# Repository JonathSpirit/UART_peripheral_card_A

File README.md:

# UART_peripheral_card_A

Copyright (C) 2021 Guillaume Guillet\
Licensed under CERN-OHL-W v2 or later

<table border="0px">
<tr>
<td>
This source describes Open Hardware and is licensed under the CERN-OHL-W v2 or later.
</td>
</tr>
<tr>
<td>
You may redistribute and modify this documentation and make products
using it under the terms of the CERN-OHL-W v2 (https:/cern.ch/cern-ohl).
This documentation is distributed WITHOUT ANY EXPRESS OR IMPLIED
WARRANTY, INCLUDING OF MERCHANTABILITY, SATISFACTORY QUALITY
AND FITNESS FOR A PARTICULAR PURPOSE. Please see the CERN-OHL-W v2
for applicable conditions.
</td>
</tr>
</table>

Made with [Kicad](https://kicad.org/)

## Description
A UART peripheral card compatible with [PP1 standard](https://github.com/JonathSpirit/GComputer_standard).
This is a homemade without any microcontroller UART board that can transmit and receive in fixed 9600 baud rate and full-duplex.

## Stats

\
\
\

## Main features

- Follow the [PP1](https://github.com/JonathSpirit/GComputer_standard) standard.

- Fixed 9600 baud rate.

- Full duplex.

- 1 byte receive/transmit buffer.

- Compatible CMOS/TTL logic level.

## Documents
[Schematics (.pdf)](documents/UART_peripheral_card_A_schematics.pdf)

[Materials (.pdf)](documents/UART_peripheral_card_A_materials.pdf)

## Contributing / Questions
Please see [Contributing file](CONTRIBUTING.md)

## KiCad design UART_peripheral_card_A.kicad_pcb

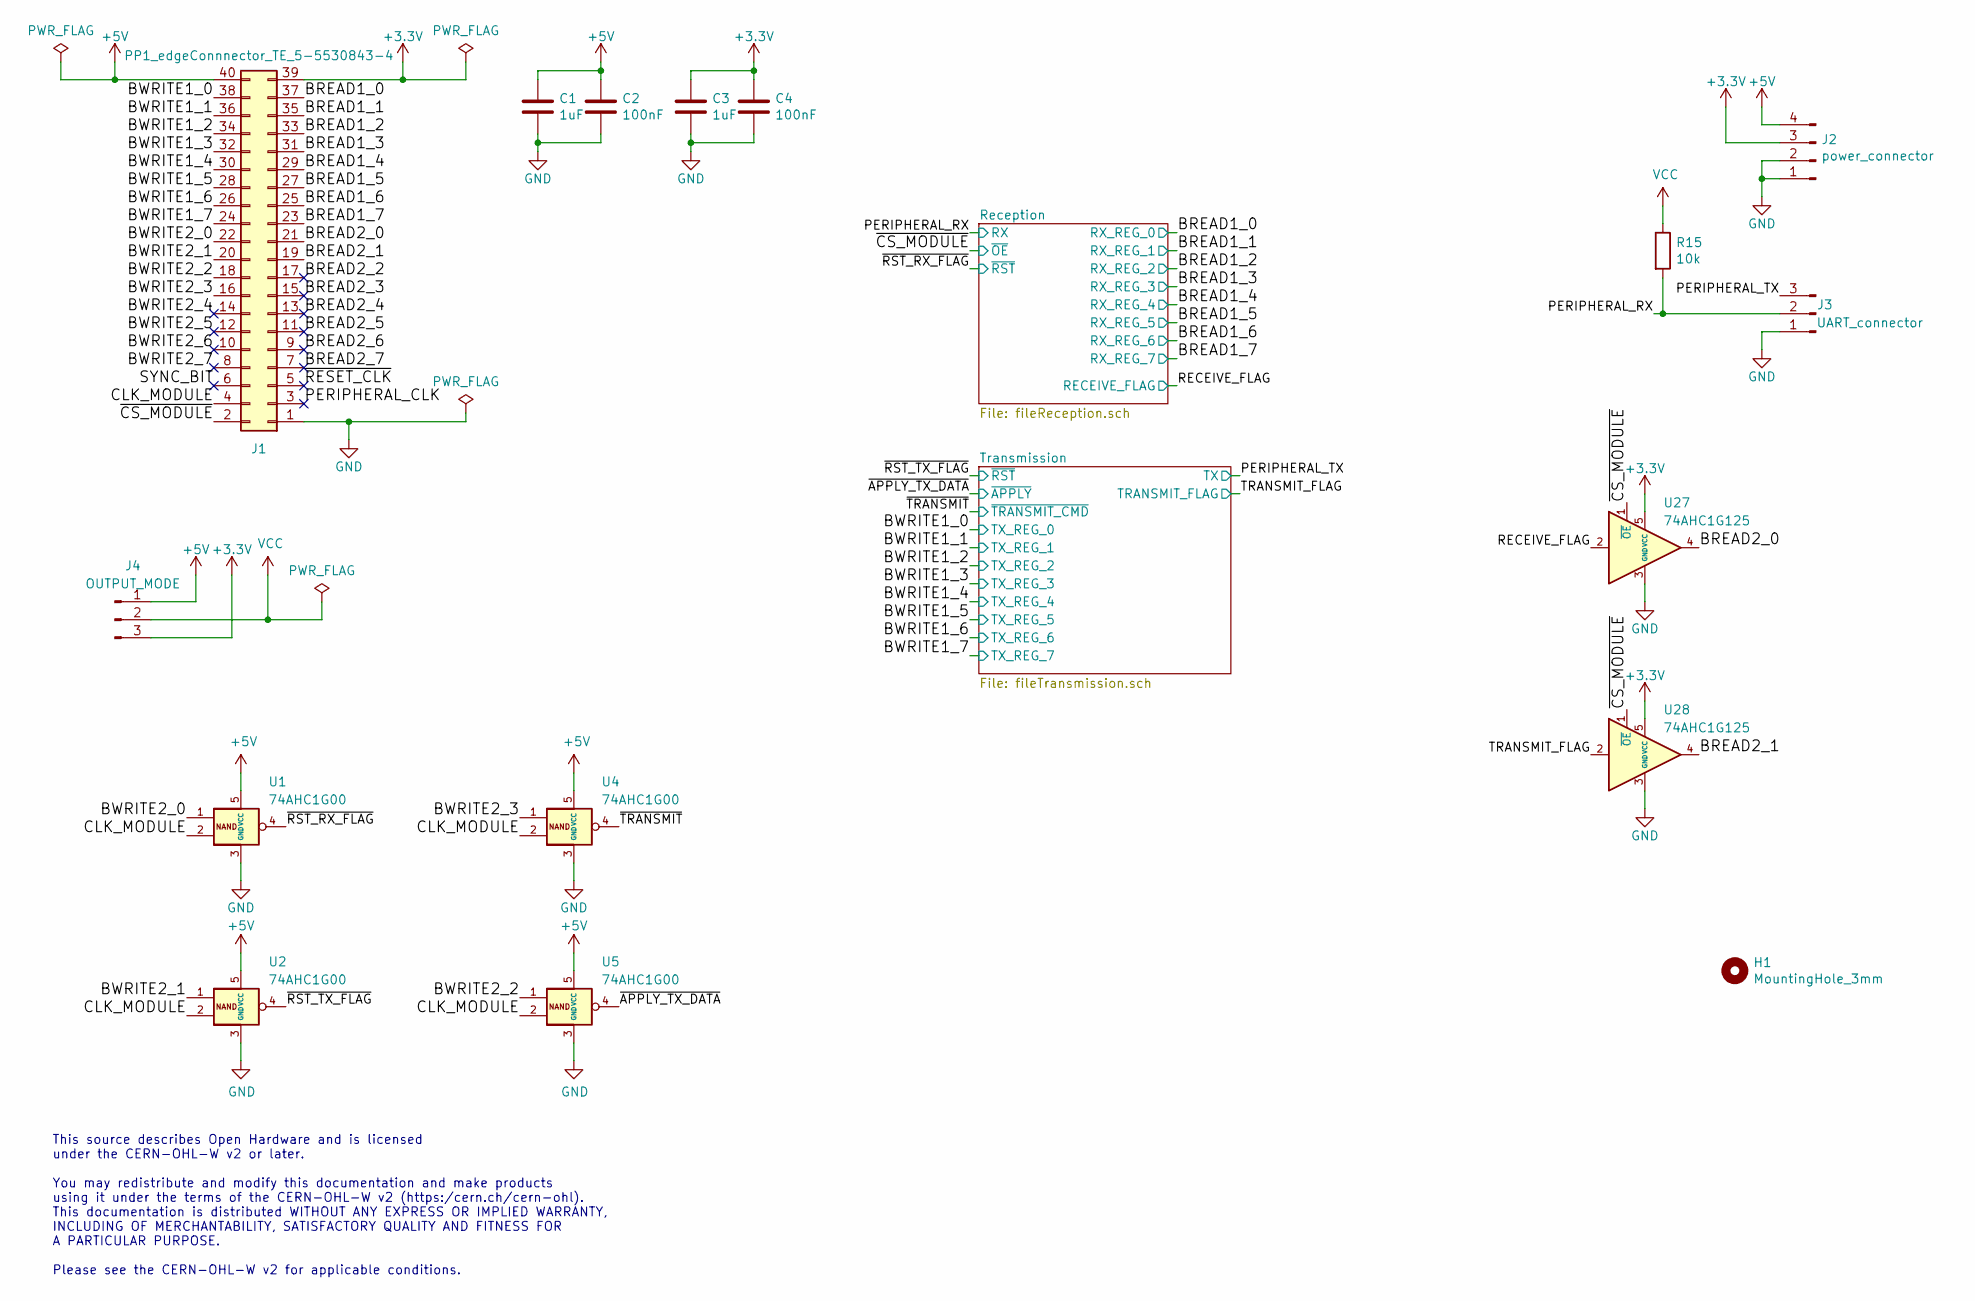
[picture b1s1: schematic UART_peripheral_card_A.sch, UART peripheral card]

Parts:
C1, C3: 1uF; C_0805_2012Metric
C2, C4: 100nF; C_0805_2012Metric
H1: MountingHole_3mm
J1: PP1_edgeConnnector_TE_5-5530843-4; TE_5-5530843-4_edge
J2: power_connector; PinHeader_1x04_P2.54mm_Horizontal
J3: UART_connector; PinHeader_1x03_P2.54mm_Horizontal
J4: OUTPUT_MODE; PinHeader_1x03_P2.54mm_Vertical
R15: 10k; R_0805_2012Metric
U1, U2, U4, U5: 74AHC1G00; SOT-23-5
U27, U28: 74AHC1G125; SOT-23-5

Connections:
+3V3: C3.1, C4.1, J1.39, J2.3, J4.3, U27.5 (VCC), U28.5 (VCC); also elsewhere on the board
+5V: C1.1, C2.1, J1.40, J2.4, J4.1, U1.5 (VCC), U2.5 (VCC), U4.5 (VCC), U5.5 (VCC); also elsewhere on the board
/BREAD1_0: J1.37; also elsewhere on the board
/BREAD1_1: J1.35; also elsewhere on the board
/BREAD1_2: J1.33; also elsewhere on the board
/BREAD1_3: J1.31; also elsewhere on the board
/BREAD1_4: J1.29; also elsewhere on the board
/BREAD1_5: J1.27; also elsewhere on the board
/BREAD1_6: J1.25; also elsewhere on the board
/BREAD1_7: J1.23; also elsewhere on the board
/BREAD2_0: J1.21, U27.4
/BREAD2_1: J1.19, U28.4
/BREAD2_2: J1.17
/BREAD2_3: J1.15
/BREAD2_4: J1.13
/BREAD2_5: J1.11
/BREAD2_6: J1.9
/BREAD2_7: J1.7
/BWRITE1_0: J1.38; also elsewhere on the board
/BWRITE1_1: J1.36; also elsewhere on the board
/BWRITE1_2: J1.34; also elsewhere on the board
/BWRITE1_3: J1.32; also elsewhere on the board
/BWRITE1_4: J1.30; also elsewhere on the board
/BWRITE1_5: J1.28; also elsewhere on the board
/BWRITE1_6: J1.26; also elsewhere on the board
/BWRITE1_7: J1.24; also elsewhere on the board
/BWRITE2_0: J1.22, U1.1
/BWRITE2_1: J1.20, U2.1
/BWRITE2_2: J1.18, U5.1
/BWRITE2_3: J1.16, U4.1
/BWRITE2_4: J1.14
/BWRITE2_5: J1.12
/BWRITE2_6: J1.10
/BWRITE2_7: J1.8
/CLK_MODULE: J1.4, U1.2, U2.2, U4.2, U5.2
/PERIPHERAL_CLK: J1.3
/PERIPHERAL_RX: J3.2, R15.2; also elsewhere on the board
/PERIPHERAL_TX: J3.3; also elsewhere on the board
/RECEIVE_FLAG: U27.2; also elsewhere on the board
/SYNC_BIT: J1.6
/TRANSMIT_FLAG: U28.2; also elsewhere on the board
/~APPLY_TX_DATA: U5.4; also elsewhere on the board
/~CS_MODULE: J1.2, U27.1 (~OE), U28.1 (~OE); also elsewhere on the board
/~RESET_CLK: J1.5
/~RST_RX_FLAG: U1.4; also elsewhere on the board
/~RST_TX_FLAG: U2.4; also elsewhere on the board
/~TRANSMIT: U4.4; also elsewhere on the board
GND: C1.2, C2.2, C3.2, C4.2, J1.1, J2.1, J2.2, J3.1, U1.3 (GND), U2.3 (GND), U4.3 (GND), U5.3 (GND), U27.3 (GND), U28.3 (GND); also elsewhere on the board
VCC: J4.2, R15.1; also elsewhere on the board

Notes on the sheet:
This source describes Open Hardware and is licensed under the CERN-OHL-W v2 or later. You may redistribute and modify this documentation and make products using it under the terms of the CERN-OHL-W v2 (https:/cern.ch/cern-ohl). This documentation is distributed WITHOUT ANY EXPRESS OR IMPLIED WARRAN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

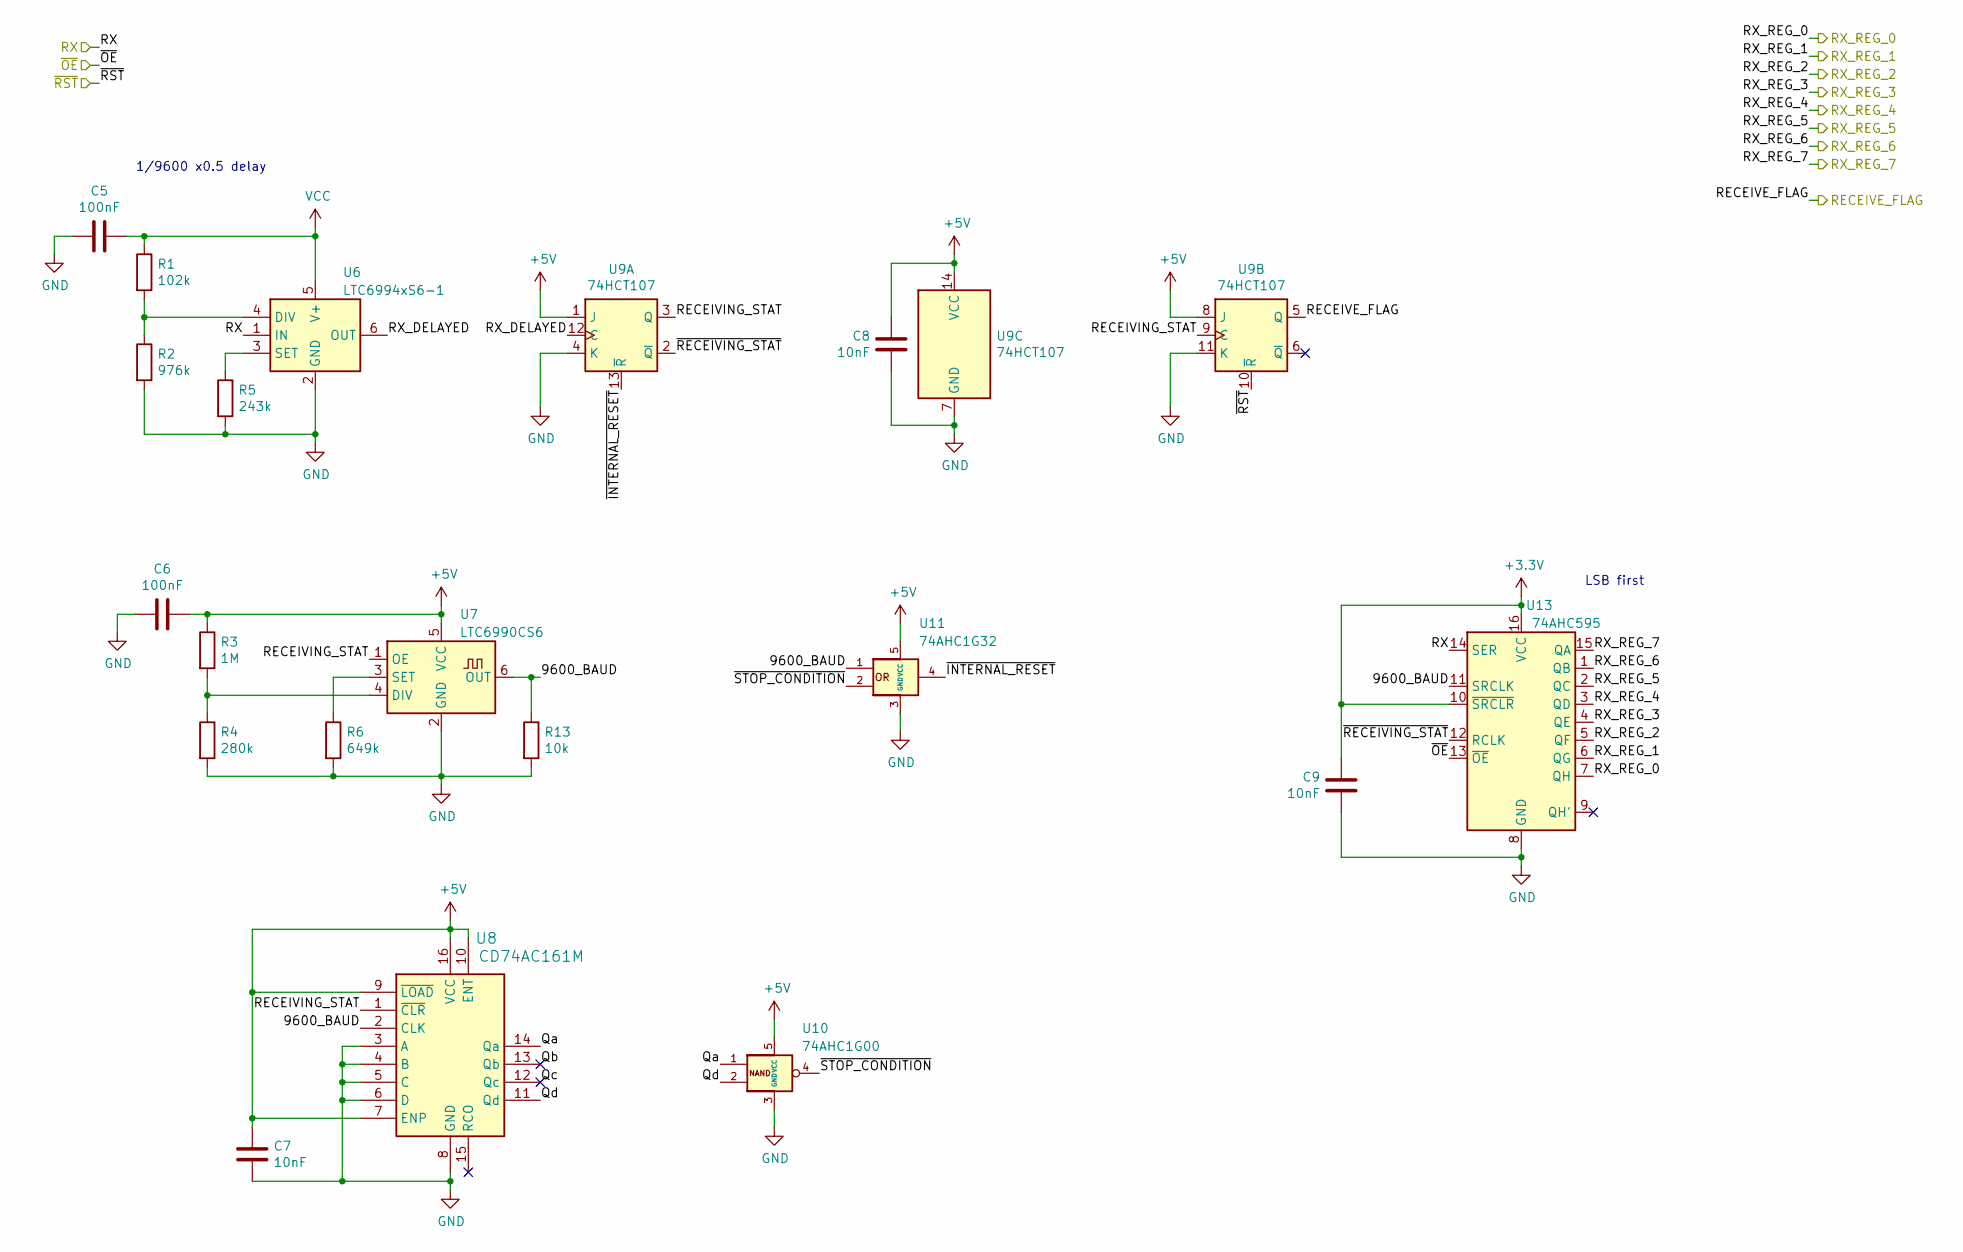
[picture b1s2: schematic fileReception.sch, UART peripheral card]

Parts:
C5, C6: 100nF; C_0805_2012Metric
C7, C8, C9: 10nF; C_0805_2012Metric
R1: 102k; R_0805_2012Metric
R2: 976k; R_0805_2012Metric
R3: 1M; R_0805_2012Metric
R4: 280k; R_0805_2012Metric
R5: 243k; R_0805_2012Metric
R6: 649k; R_0805_2012Metric
R13: 10k; R_0805_2012Metric
U6: LTC6994xS6-1; SOT-23-6
U7: LTC6990CS6; SOT-23-6
U8: CD74AC161M; SOP-16_3.9x9.9mm_P1.27mm
U9: 74HCT107; SO-14_3.9x8.65mm_P1.27mm
U10: 74AHC1G00
U11: 74AHC1G32; SOT-23-5
U13: 74AHC595; SOIC-16_3.9x9.9mm_P1.27mm

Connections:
+3V3: C9.2, U13.10 (~SRCLR), U13.16 (VCC); also elsewhere on the board
+5V: C6.1, C7.2, C8.2, R3.1, U7.5 (VCC), U8.7 (ENP), U8.9 (~LOAD), U8.10 (ENT), U8.16 (VCC), U9.1 (J), U9.8 (J), U9.14 (VCC), U10.5 (VCC), U11.5 (VCC); also elsewhere on the board
/BREAD1_0: U13.7 (QH); also elsewhere on the board
/BREAD1_1: U13.6 (QG); also elsewhere on the board
/BREAD1_2: U13.5 (QF); also elsewhere on the board
/BREAD1_3: U13.4 (QE); also elsewhere on the board
/BREAD1_4: U13.3 (QD); also elsewhere on the board
/BREAD1_5: U13.2 (QC); also elsewhere on the board
/BREAD1_6: U13.1 (QB); also elsewhere on the board
/BREAD1_7: U13.15 (QA); also elsewhere on the board
/PERIPHERAL_RX: U6.1 (IN), U13.14 (SER); also elsewhere on the board
/RECEIVE_FLAG: U9.5 (Q); also elsewhere on the board
/Reception/9600_BAUD: R13.1, U7.6 (OUT), U8.2 (CLK), U11.1, U13.11 (SRCLK)
/Reception/Qa: U8.14 (Qa), U10.1
/Reception/Qb: U8.13 (Qb)
/Reception/Qc: U8.12 (Qc)
/Reception/Qd: U8.11 (Qd), U10.2
/Reception/RECEIVING_STAT: U7.1 (OE), U8.1 (~CLR), U9.3 (Q), U9.9 (C)
/Reception/RX_DELAYED: U6.6 (OUT), U9.12 (C)
/Reception/~INTERNAL_RESET: U9.13 (~R), U11.4
/Reception/~RECEIVING_STAT: U9.2 (~Q), U13.12 (RCLK)
/Reception/~STOP_CONDITION: U10.4, U11.2
/~CS_MODULE: U13.13 (~OE); also elsewhere on the board
/~RST_RX_FLAG: U9.10 (~R); also elsewhere on the board
GND: C5.2, C6.2, C7.1, C8.1, C9.1, R2.2, R4.2, R5.2, R6.2, R13.2, U6.2 (GND), U7.2 (GND), U8.3 (A), U8.4 (B), U8.5 (C), U8.6 (D), U8.8 (GND), U9.4 (K), U9.7 (GND), U9.11 (K), U10.3 (GND), U11.3 (GND), U13.8 (GND); also elsewhere on the board
unnamed: R1.2, R2.1, U6.4 (DIV)
unnamed: R3.2, R4.1, U7.4 (DIV)
unnamed: R5.1, U6.3 (SET)
unnamed: R6.1, U7.3 (SET)
VCC: C5.1, R1.1, U6.5 (V+); also elsewhere on the board

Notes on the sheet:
1/9600 x0.5 delay
LSB first

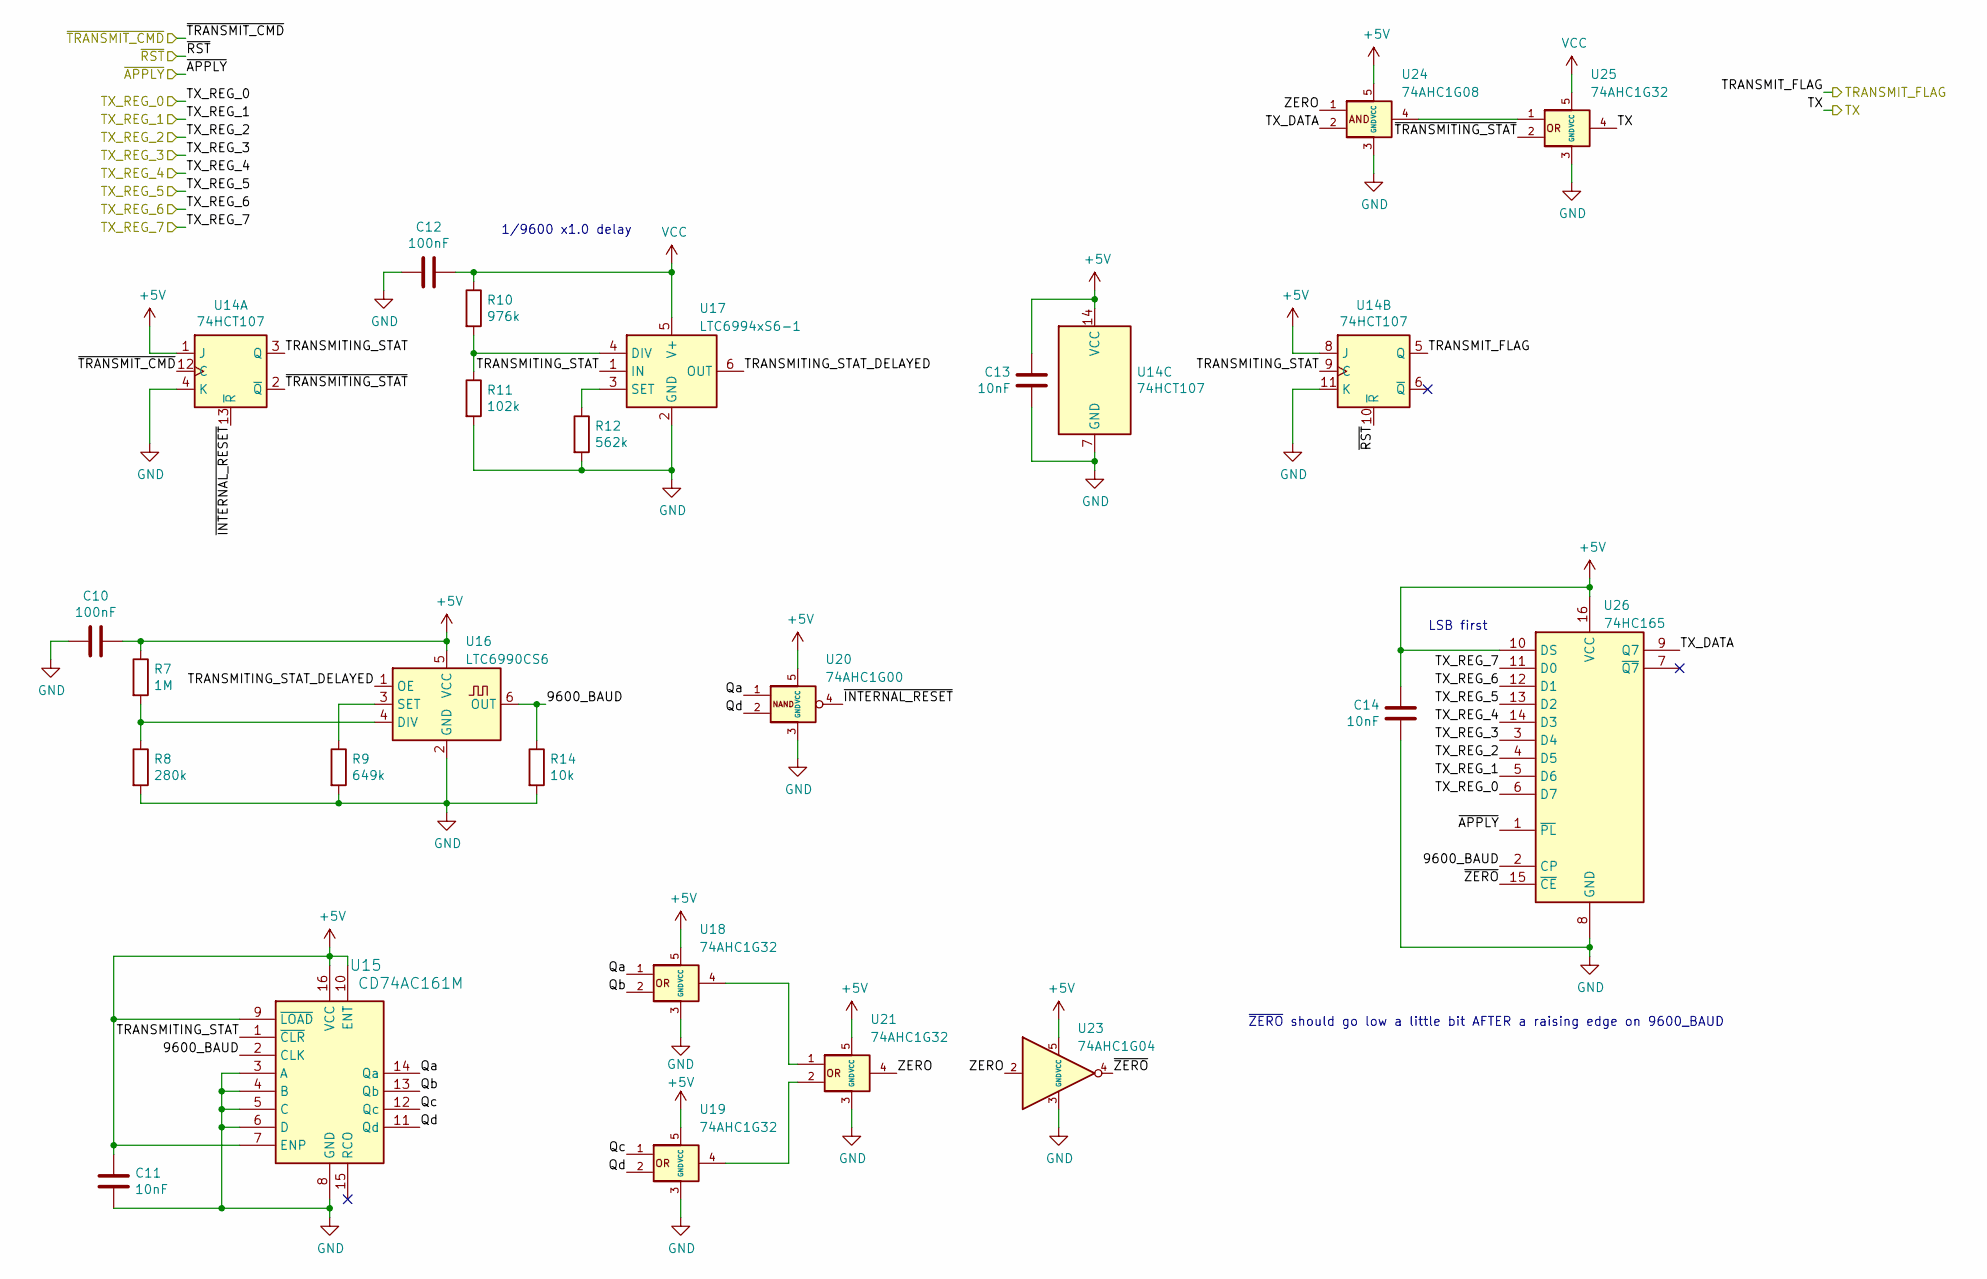
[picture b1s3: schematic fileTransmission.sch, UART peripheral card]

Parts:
C10, C12: 100nF; C_0805_2012Metric
C11, C13, C14: 10nF; C_0805_2012Metric
R7: 1M; R_0805_2012Metric
R8: 280k; R_0805_2012Metric
R9: 649k; R_0805_2012Metric
R10: 976k; R_0805_2012Metric
R11: 102k; R_0805_2012Metric
R12: 562k; R_0805_2012Metric
R14: 10k; R_0805_2012Metric
U14: 74HCT107; SO-14_3.9x8.65mm_P1.27mm
U15: CD74AC161M; SOP-16_3.9x9.9mm_P1.27mm
U16: LTC6990CS6; SOT-23-6
U17: LTC6994xS6-1; SOT-23-6
U18, U19, U21, U25: 74AHC1G32; SOT-23-5
U20: 74AHC1G00
U23: 74AHC1G04; SOT-23-5
U24: 74AHC1G08; SOT-23-5
U26: 74HC165; SOIC-16_3.9x9.9mm_P1.27mm

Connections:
+5V: C10.1, C11.2, C13.2, C14.2, R7.1, U14.1 (J), U14.8 (J), U14.14 (VCC), U15.7 (ENP), U15.9 (~LOAD), U15.10 (ENT), U15.16 (VCC), U16.5 (VCC), U18.5 (VCC), U19.5 (VCC), U20.5 (VCC), U21.5 (VCC), U23.5 (VCC), U24.5 (VCC), U26.10 (DS), U26.16 (VCC); also elsewhere on the board
/BWRITE1_0: U26.6 (D7); also elsewhere on the board
/BWRITE1_1: U26.5 (D6); also elsewhere on the board
/BWRITE1_2: U26.4 (D5); also elsewhere on the board
/BWRITE1_3: U26.3 (D4); also elsewhere on the board
/BWRITE1_4: U26.14 (D3); also elsewhere on the board
/BWRITE1_5: U26.13 (D2); also elsewhere on the board
/BWRITE1_6: U26.12 (D1); also elsewhere on the board
/BWRITE1_7: U26.11 (D0); also elsewhere on the board
/PERIPHERAL_TX: U25.4; also elsewhere on the board
/TRANSMIT_FLAG: U14.5 (Q); also elsewhere on the board
/Transmission/9600_BAUD: R14.1, U15.2 (CLK), U16.6 (OUT), U26.2 (CP)
/Transmission/Qa: U15.14 (Qa), U18.1, U20.1
/Transmission/Qb: U15.13 (Qb), U18.2
/Transmission/Qc: U15.12 (Qc), U19.1
/Transmission/Qd: U15.11 (Qd), U19.2, U20.2
/Transmission/TRANSMITING_STAT: U14.3 (Q), U14.9 (C), U15.1 (~CLR), U17.1 (IN)
/Transmission/TRANSMITING_STAT_DELAYED: U16.1 (OE), U17.6 (OUT)
/Transmission/TX_DATA: U24.2, U26.9 (Q7)
/Transmission/ZERO: U21.4, U23.2, U24.1
/Transmission/~INTERNAL_RESET: U14.13 (~R), U20.4
/Transmission/~TRANSMITING_STAT: U14.2 (~Q), U25.2
/Transmission/~ZERO: U23.4, U26.15 (~CE)
/~APPLY_TX_DATA: U26.1 (~PL); also elsewhere on the board
/~RST_TX_FLAG: U14.10 (~R); also elsewhere on the board
/~TRANSMIT: U14.12 (C); also elsewhere on the board
GND: C10.2, C11.1, C12.2, C13.1, C14.1, R8.2, R9.2, R11.2, R12.2, R14.2, U14.4 (K), U14.7 (GND), U14.11 (K), U15.3 (A), U15.4 (B), U15.5 (C), U15.6 (D), U15.8 (GND), U16.2 (GND), U17.2 (GND), U18.3 (GND), U19.3 (GND), U20.3 (GND), U21.3 (GND), U23.3 (GND), U24.3 (GND), U25.3 (GND), U26.8 (GND); also elsewhere on the board
unnamed: R7.2, R8.1, U16.4 (DIV)
unnamed: R9.1, U16.3 (SET)
unnamed: R10.2, R11.1, U17.4 (DIV)
unnamed: R12.1, U17.3 (SET)
unnamed: U18.4, U21.1
unnamed: U19.4, U21.2
unnamed: U24.4, U25.1
VCC: C12.1, R10.1, U17.5 (V+), U25.5 (VCC); also elsewhere on the board

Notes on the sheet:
1/9600 x1.0 delay
~ZERO~ should go low a little bit AFTER a raising edge on 9600_BAUD
LSB first

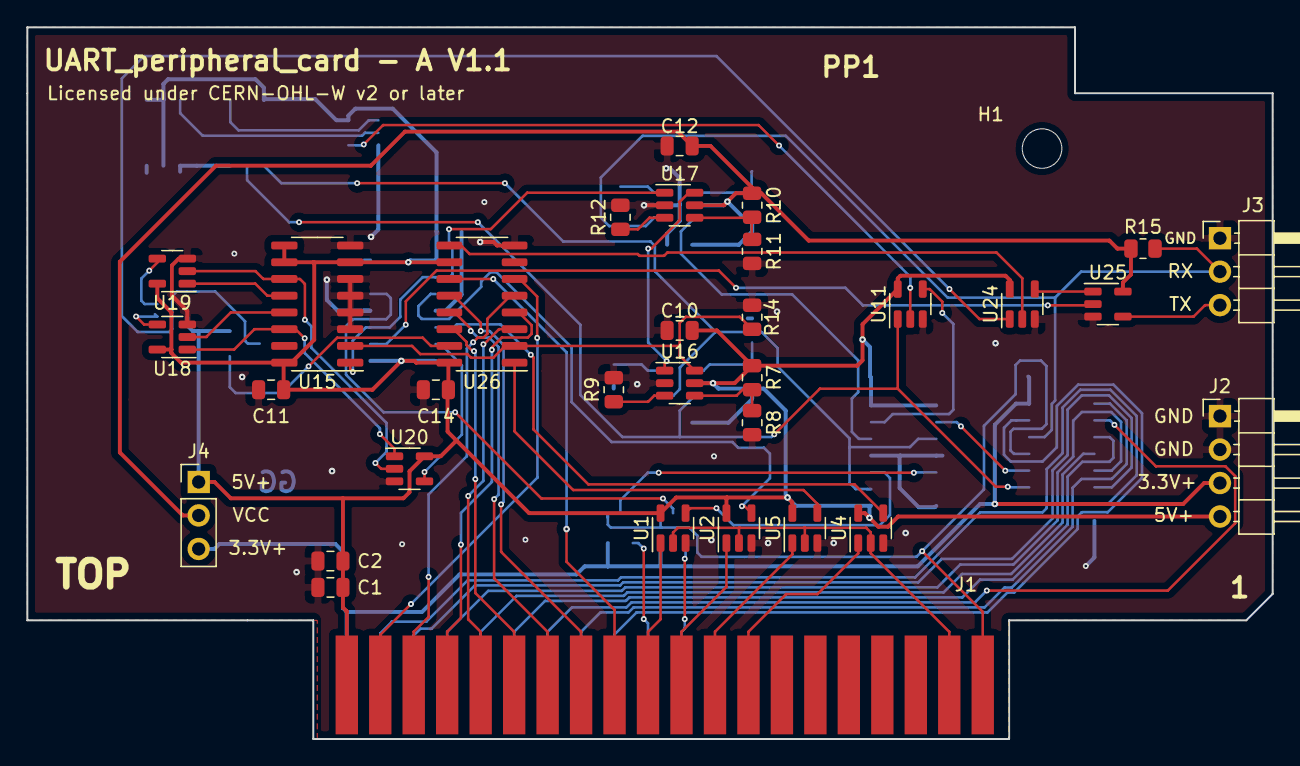
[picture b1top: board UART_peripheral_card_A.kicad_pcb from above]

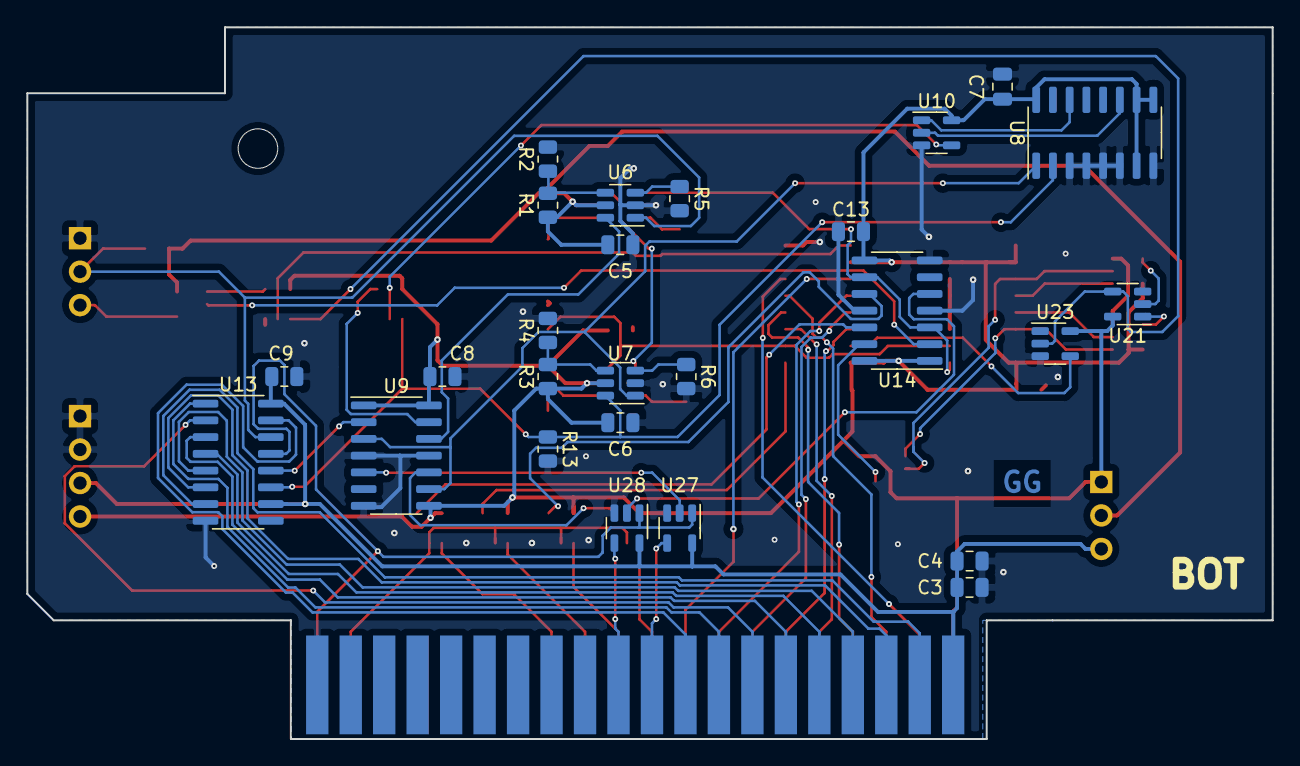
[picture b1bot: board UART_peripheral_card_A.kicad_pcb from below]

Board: 2 copper layers, 94.5 x 54.0 mm, 59 parts (26 on the bottom side), 67 nets.

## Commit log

2021-02-22 Initial push
2021-02-24 Finish pcb routing
2021-02-24 Add images
2021-02-24 funding file
2021-05-11 Fixing LSB first issue #1
2021-05-11 Fix active high enable pin #2 by replacing 74AHC1G126 with 74AHC1G125
2021-05-11 Removing the need of U3 inverter #3 replacing U1,U2,U4,U5 with 74AHC1G00
2021-05-11 Adding pull-up on RX pin #4
2021-05-11 Optimize gates count by replacing AND,INV with NAND
2021-05-11 Set date and version (schematics)
2021-05-11 netlist, association, CHANGELOG
2021-05-13 BOM V1.1
2021-05-19 Modify trackWidth,via diameter, first PCB 1.1 pass
2021-05-20 Fix LSB issue on waveforms #1
2021-05-20 CHANGELOG
2021-05-20 Exporting new BOM, schematics in pdf
2021-05-20 Exporting new images
2021-05-20 Exporting new PCB*.pdf
2021-05-20 Exporting new fabrication files

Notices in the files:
UART_peripheral_card_A.kicad_pcb:
Copyright Guillaume Guillet 2021
